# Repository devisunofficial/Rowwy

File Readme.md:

# Rowwy
Rowwy is a hand-movement control car which uses Mecanum wheels.

### CAD Model:
It has two seperate bodies.

Controller : 

Rowwy : 

### PCB:
Here's my PCB! It was made in KiCad. 

Schematic : 
PCB Footprint : 

### Firmware Overview:
Current version of Firmware is underdevelopment as it has not be implemeted in real life.
This car and controller uses C++ firmware and Arduino IDE for Flashing.

### Assembly Instructions :
1. Flash Firmware in XIAO ESP32 and Wroom Dev-board
2. Solder Motors, Devboard, Battery of car 
3. Solder Gyro-sensor, Flex-Sensor, Battery of controller
4. Check If Everything Works or not, also update the code depending on soldered pins
5. Glue togetther the controller enclosure and bracelet. Also Glue together battery and all circuits on Rowwy's base plate
6. Screw motor holder to base plate and enjoy the ride.

### BOM Table
|Name|Use|Quantity|Distributer|Total Cost(USD)|Link|
|-----|---|-------|-----------|-----|---|
|18650 battery |Power Source for Car|1|Robu|3|13.2|[Link](https://robu.in/product/samsung-inr18650-25r-2500mah-li-ion-battery/)|
|PCB|Main-Circuit|1|JLCPCB|32|--|
|XIAO ESP32|Controller|1|Robu|7.2|[Link](https://robu.in/product/seeed-studio-xiao-esp32c3-tiny-mcu-board-with-wi-fi-and-ble-battery-charge-supported-power-efficiency-and-rich-interface/)|
|Wroom ESP32 Dev Board|Reciever for Car|1|Robu|7.4|[Link](https://robu.in/product/smartelex-esp-wroom-32-wifi-bluetooth-networking-development-board-1-pcs/)|
|Mecanum Wheels|For Motion|1|Robu|5.3|[Link](https://robu.in/product/80mm-a-mecanum-wheel-compatible-with-6-7mm-coupling-pack-of-4-yellow/)|
|N20 geared Motor|Powering Motion|4|Robu|6.7|[Link](https://robu.in/product/n20-12v-600-rpm-micro-metal-gear-motor/)|
|Battery(1)|For Controller|1|Robu|2|[Link](https://robu.in/product/nova-303040-400mah-3-7v-micro-lipo-battery-pack/)|
|Flex Sensor|Handbreak Functionality|1|Robu|7.3|[Link](https://robu.in/product/flex-sensor-2-2-bend-sensor-hand-gesture-recognition/)|
|MPU6050|Calculating Handmovement|1|Robu|1.5|[Link](https://robu.in/product/mpu6500-gyroscope-accelerometer-digital-motion-processor-dmp-6-axis-motion-sensor-with-i2c-spi-interface/)|
|battery holder|To hold 18650 battery|1|Robu|0.3|[Link](https://robu.in/product/black-plastic-storage-box-case-holder-battery-3-x-18650-cell-box-without-cover/)|
|18650 charger|To charge 18650 battery|1|Amazon|2.1|[Link](https://www.amazon.in/TESTIN-ELECTRONICS-Battery-Charger-Charger-1Slot/dp/B0G4JR7FVW?source=ps-sl-shoppingads-lpcontext&psc=1&smid=A1LULBHI7A07S5)|

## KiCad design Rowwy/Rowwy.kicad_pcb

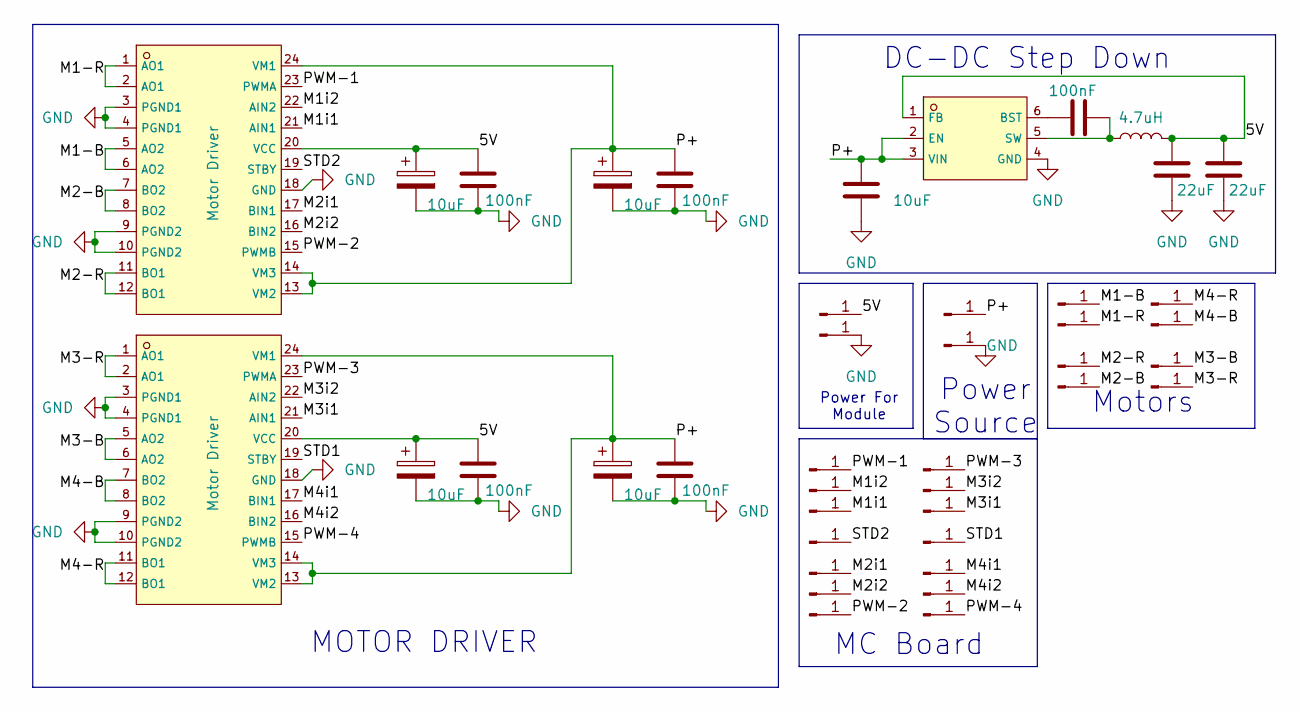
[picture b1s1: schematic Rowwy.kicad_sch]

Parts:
C1, C5, C7, C9, C11: 10uF; C_0603_1608Metric
C2, C6, C8, C10, C12: 100nF; C_0603_1608Metric
C3, C4: 22uF; C_0603_1608Metric
J1, J2, J3, J4, J5, J6, J7, J8, J9, J10, J11, J12, J13, J14, J15, J16, J17, J18, J19, J20, J21, J22, J23, J24, J25, J26: Conn_01x01_Pin; SolderWirePad_1x01_SMD_2x4mm
L1: 4.7uH; L_0603_1608Metric
U1, U3: Motor Driver; C88224_SSOP-24_L8_4-W5_8-P0_65-LS7_8-BL; LCSC C88224
U2: AP63203WU-7; C780769_TSOT-26_L2_9-W1_6-P0_95-LS2_8-BL; LCSC C780769

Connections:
/5V: C3.1, C4.1, C5.1, C6.1, C9.1, C10.1, J3.1 (Pin_1_1), L1.2, U1.20 (VCC), U2.1 (FB), U3.20 (VCC)
/M1-B: J5.1 (Pin_1_1), U1.5 (AO2), U1.6 (AO2)
/M1-R: J6.1 (Pin_1_1), U1.1 (AO1), U1.2 (AO1)
/M1i1: J15.1 (Pin_1_1), U1.21 (AIN1)
/M1i2: J14.1 (Pin_1_1), U1.22 (AIN2)
/M2-B: J8.1 (Pin_1_1), U1.7 (BO2), U1.8 (BO2)
/M2-R: J7.1 (Pin_1_1), U1.11 (BO1), U1.12 (BO1)
/M2i1: J18.1 (Pin_1_1), U1.17 (BIN1)
/M2i2: J19.1 (Pin_1_1), U1.16 (BIN2)
/M3-B: J11.1 (Pin_1_1), U3.5 (AO2), U3.6 (AO2)
/M3-R: J12.1 (Pin_1_1), U3.1 (AO1), U3.2 (AO1)
/M3i1: J26.1 (Pin_1_1), U3.21 (AIN1)
/M3i2: J25.1 (Pin_1_1), U3.22 (AIN2)
/M4-B: J10.1 (Pin_1_1), U3.7 (BO2), U3.8 (BO2)
/M4-R: J9.1 (Pin_1_1), U3.11 (BO1), U3.12 (BO1)
/M4i1: J21.1 (Pin_1_1), U3.17 (BIN1)
/M4i2: J22.1 (Pin_1_1), U3.16 (BIN2)
/P+: C1.1, C7.1, C8.1, C11.1, C12.1, J1.1 (Pin_1_1), U1.13 (VM2), U1.14 (VM3), U1.24 (VM1), U2.2 (EN), U2.3 (VIN), U3.13 (VM2), U3.14 (VM3), U3.24 (VM1)
/PWM-1: J13.1 (Pin_1_1), U1.23 (PWMA)
/PWM-2: J20.1 (Pin_1_1), U1.15 (PWMB)
/PWM-3: J24.1 (Pin_1_1), U3.23 (PWMA)
/PWM-4: J23.1 (Pin_1_1), U3.15 (PWMB)
/STD1: J17.1 (Pin_1_1), U3.19 (STBY)
/STD2: J16.1 (Pin_1_1), U1.19 (STBY)
GND: C1.2, C3.2, C4.2, C5.2, C6.2, C7.2, C8.2, C9.2, C10.2, C11.2, C12.2, J2.1 (Pin_1_1), J4.1 (Pin_1_1), U1.3 (PGND1), U1.4 (PGND1), U1.9 (PGND2), U1.10 (PGND2), U1.18 (GND), U2.4 (GND), U3.3 (PGND1), U3.4 (PGND1), U3.9 (PGND2), U3.10 (PGND2), U3.18 (GND)
unnamed: C2.1, U2.6 (BST)
unnamed: C2.2, L1.1, U2.5 (SW)

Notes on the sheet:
Motors
DC-DC Step Down
Power Source
MC Board
Power For Module
MOTOR DRIVER

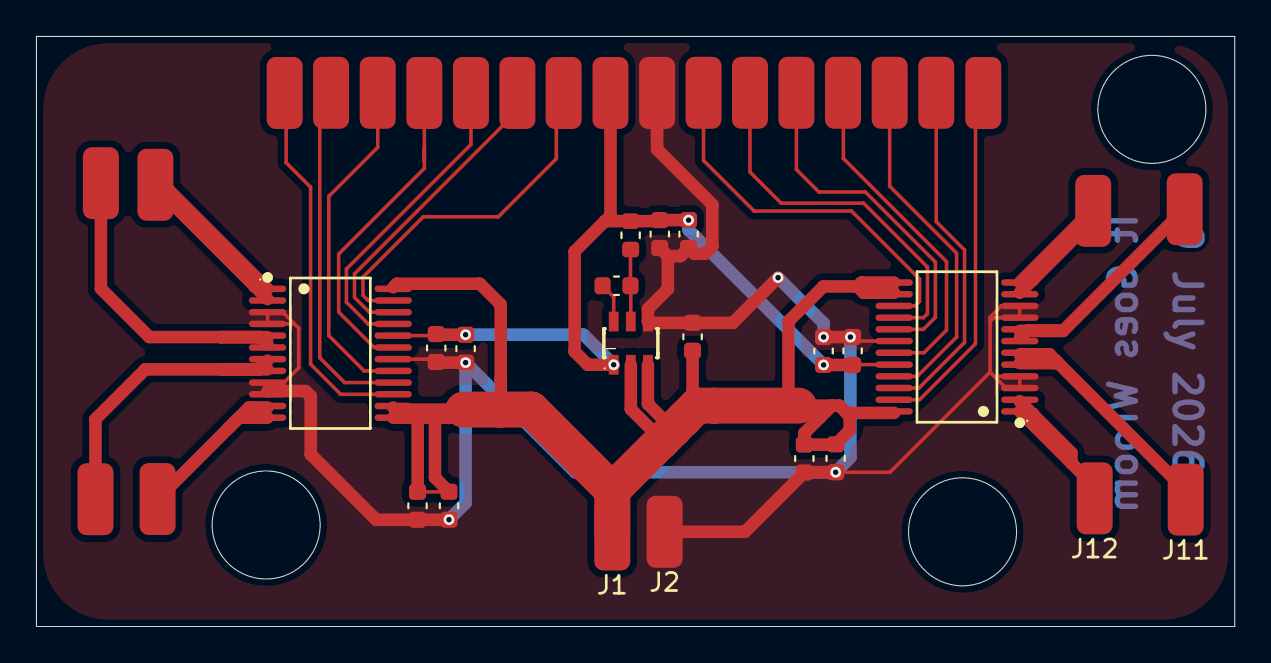
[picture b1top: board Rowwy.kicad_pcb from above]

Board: 2 copper layers, 66.6 x 32.8 mm, 42 parts (0 on the bottom side), 27 nets.

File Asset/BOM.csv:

Comment,Designator,Footprint
10uF,"C1, C5, C7, C9, C11",C_0603_1608Metric
100nF,"C2, C6, C8, C10, C12",C_0603_1608Metric
22uF,"C3, C4",C_0603_1608Metric
4.7uH,L1,L_0603_1608Metric
Motor Driver,"U1, U3",C88224_SSOP-24_L8_4-W5_8-P0_65-LS7_8-BL
AP63203WU-7,U2,C780769_TSOT-26_L2_9-W1_6-P0_95-LS2_8-BL
